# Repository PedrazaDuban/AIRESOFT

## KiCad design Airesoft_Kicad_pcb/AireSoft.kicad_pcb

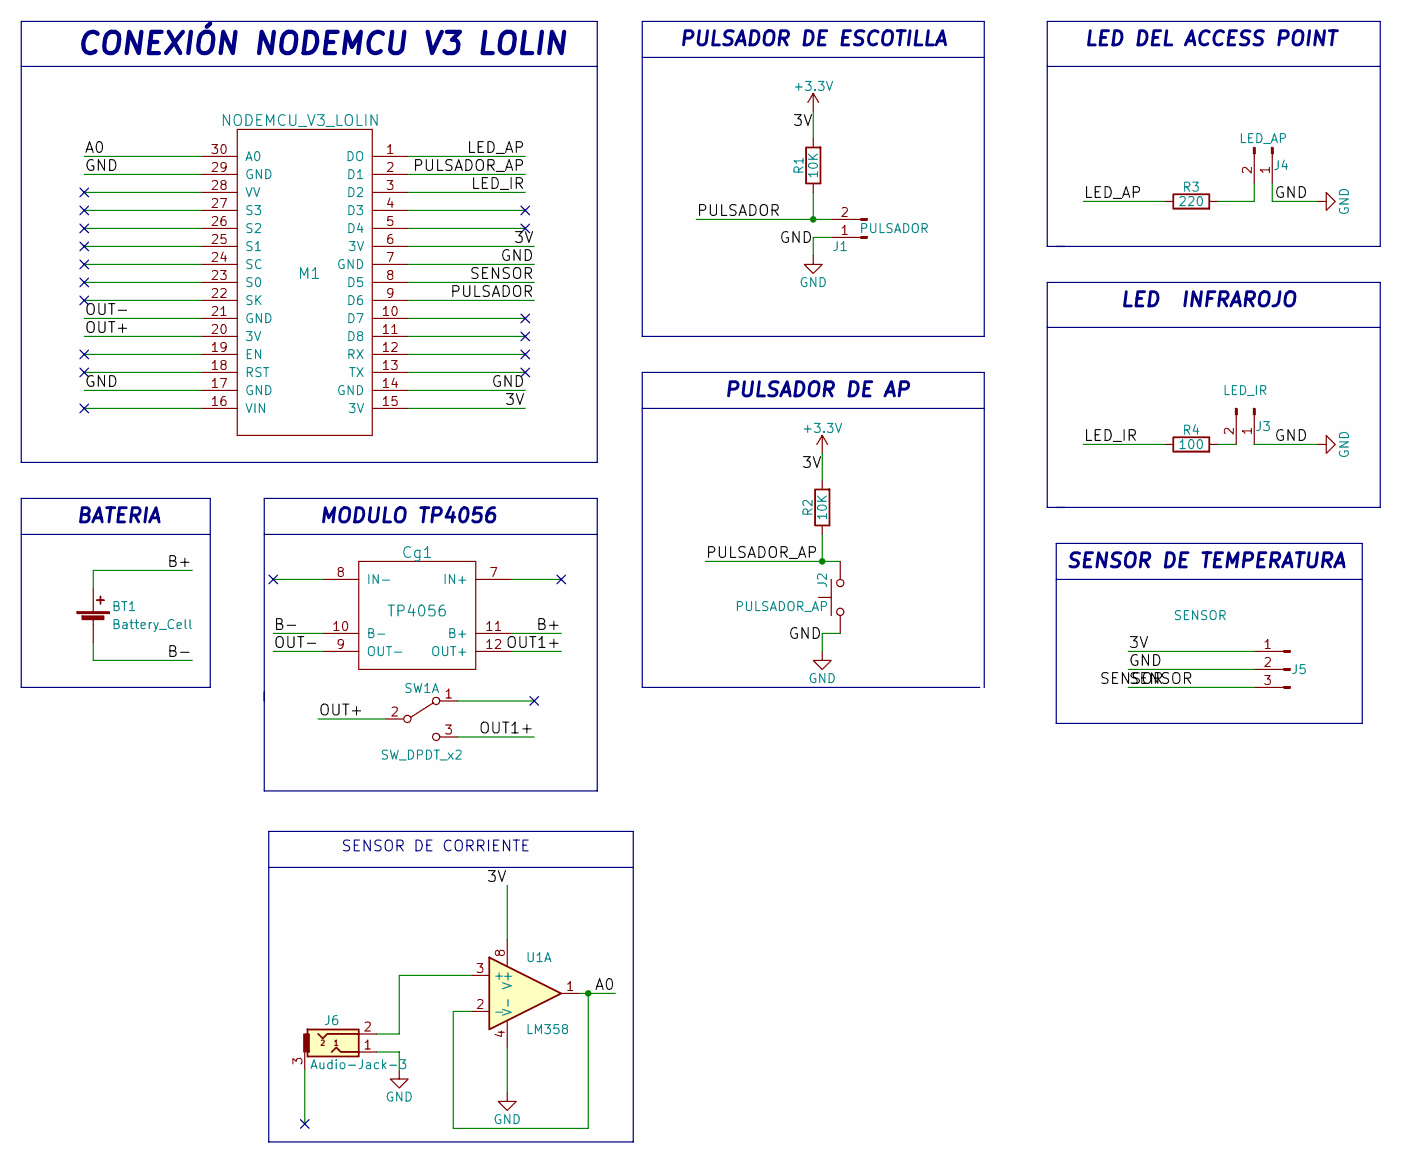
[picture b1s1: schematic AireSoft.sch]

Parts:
BT1: Battery_Cell; BATT_1X18650
Cg1: TP4056
J1: PULSADOR; Molex_KK-6410-02_02x2.54mm_Straight
J2: PULSADOR_AP; SW_Tactile_SPST_Angled_PTS645Vx83-2LFS
J3: LED_IR; Molex_KK-6410-02_02x2.54mm_Straight
J4: LED_AP; Molex_KK-6410-02_02x2.54mm_Straight
J5: SENSOR; Molex_KK-6410-03_03x2.54mm_Straight
J6: Audio-Jack-3; JACK 3,5MM
M1: NODEMCU_V3_LOLIN
R1, R2: 10K; R_Axial_DIN0207_L6.3mm_D2.5mm_P7.62mm_Horizontal
R3: 220; R_Axial_DIN0207_L6.3mm_D2.5mm_P7.62mm_Horizontal
R4: 100; R_Axial_DIN0207_L6.3mm_D2.5mm_P7.62mm_Horizontal
SW1: SW_DPDT_x2; Switch
U1: LM358; DIP-8_W7.62mm_LongPads

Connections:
+3V3: J5.1, M1.6 (3V), M1.15 (3V), R1.2, R2.2, U1.8 (V+)
/A0: M1.30 (A0), U1.1, U1.2 (-)
/B+: BT1.1 (+), Cg1.11 (B+)
/B-: BT1.2 (-), Cg1.10 (B-)
/LED_AP: M1.1 (DO), R3.1
/LED_IR: M1.3 (D2), R4.1
/OUT1+: Cg1.12 (OUT+), SW1.3 (C)
/OUT+: M1.20 (3V), SW1.2 (B)
/OUT-: Cg1.9 (OUT-), M1.21 (GND)
/PULSADOR: J1.2, M1.9 (D6), R1.1
/PULSADOR_AP: J2.2, M1.2 (D1), R2.1
/SENSOR: J5.3, M1.8 (D5)
GND: J1.1, J2.1, J3.1, J4.1, J5.2, J6.1, M1.7 (GND), M1.14 (GND), M1.17 (GND), M1.29 (GND), U1.4 (V-)
unnamed: J3.2, R4.2
unnamed: J4.2, R3.2
unnamed: J6.2, U1.3 (+)

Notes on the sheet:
CONEXIÓN NODEMCU V3 LOLIN
SENSOR DE TEMPERATURA
PULSADOR DE ESCOTILLA
PULSADOR DE AP
LED DEL ACCESS POINT
LED INFRAROJO
BATERIA
MODULO TP4056
SENSOR DE CORRIENTE

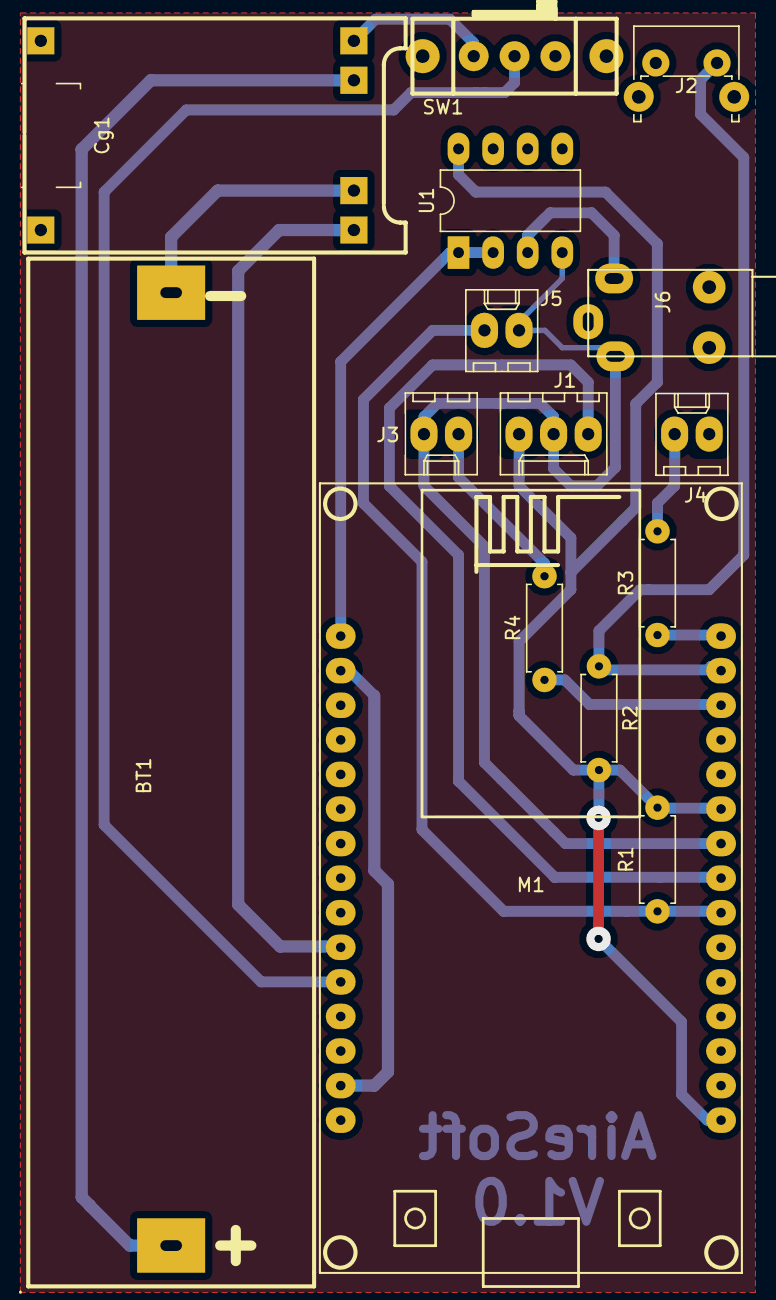
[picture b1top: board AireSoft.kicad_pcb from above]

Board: 2 copper layers, 15 parts (0 on the bottom side), 16 nets.

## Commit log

2018-09-08 Aires acondicionados Iot
    Proyecto desarrollado con Nodemcu, PHP,SQL, ARDUINO, MQTT, Y SENSORES DE TEMPERATURA.
